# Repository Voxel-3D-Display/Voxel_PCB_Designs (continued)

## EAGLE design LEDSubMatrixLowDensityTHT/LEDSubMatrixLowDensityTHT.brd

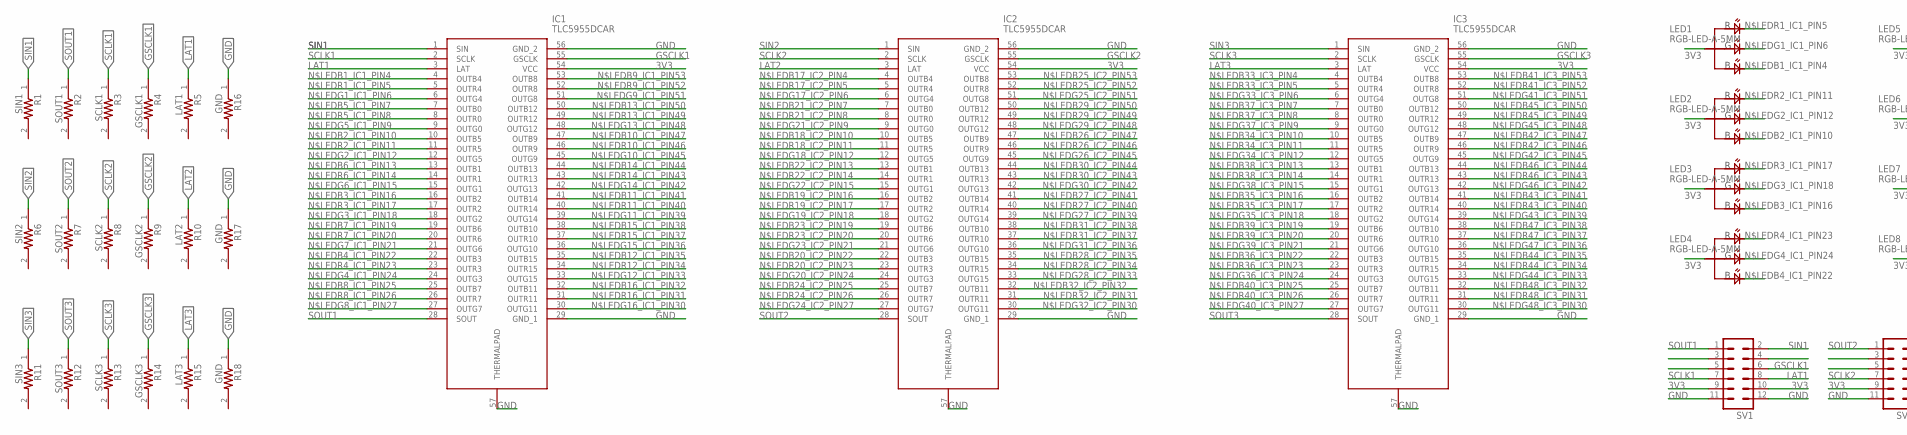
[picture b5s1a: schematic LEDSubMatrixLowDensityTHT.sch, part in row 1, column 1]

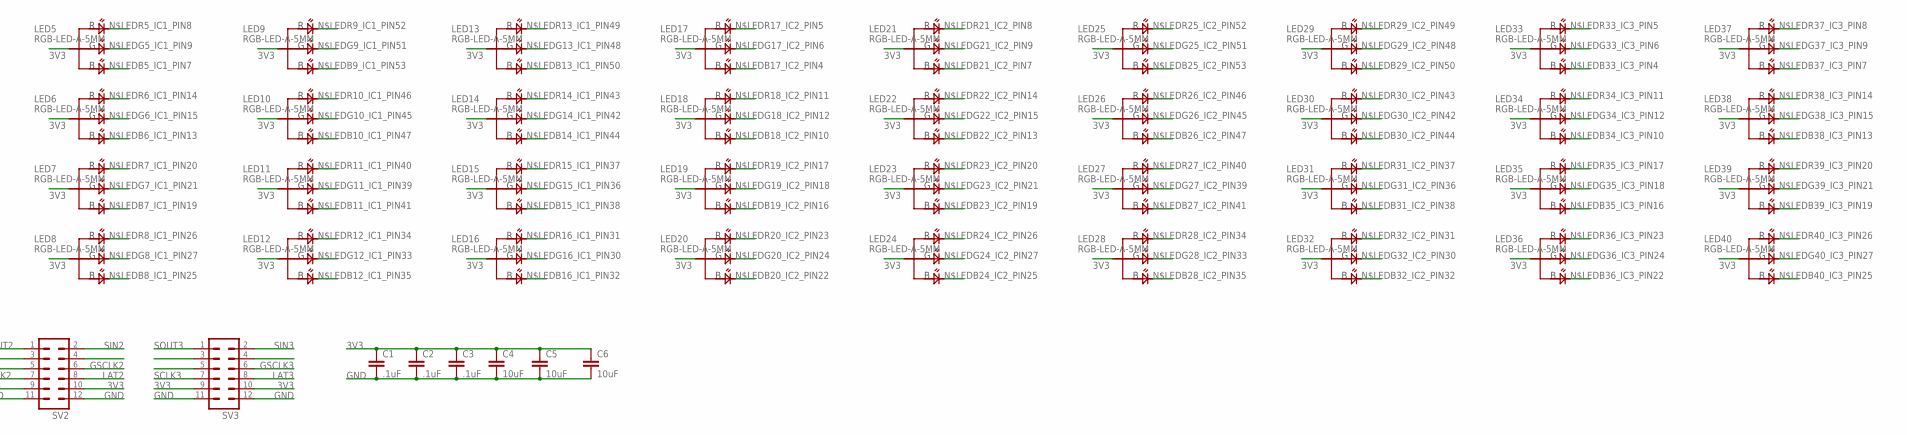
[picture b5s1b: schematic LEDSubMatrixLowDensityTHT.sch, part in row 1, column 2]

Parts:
C1, C2, C3: .1uF; C0603
C4, C5, C6: 10uF; C0805
IC1, IC2, IC3: TLC5955DCAR; SOP50P810X120-57N
LED1, LED2, LED3, LED4, LED5, LED6, LED7, LED8, LED9, LED10, LED11, LED12, LED13, LED14, LED15, LED16, LED17, LED18, LED19, LED20, LED21, LED22, LED23, LED24, LED25, LED26, LED27, LED28, LED29, LED30, LED31, LED32, LED33, LED34, LED35, LED36, LED37, LED38, LED39, LED40: RGB-LED-A-5MM; RGBLED-A-5MM
R1: SIN1; RESC3216X70N
R2: SOUT1; RESC3216X70N
R3: SCLK1; RESC3216X70N
R4: GSCLK1; RESC3216X70N
R5: LAT1; RESC3216X70N
R6: SIN2; RESC3216X70N
R7: SOUT2; RESC3216X70N
R8: SCLK2; RESC3216X70N
R9: GSCLK2; RESC3216X70N
R10: LAT2; RESC3216X70N
R11: SIN3; RESC3216X70N
R12: SOUT3; RESC3216X70N
R13: SCLK3; RESC3216X70N
R14: GSCLK3; RESC3216X70N
R15: LAT3; RESC3216X70N
R16, R17, R18: GND; RESC3216X70N
SV1, SV2, SV3: MA06-2

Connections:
3V3: C1.1, C2.1, C3.1, C4.1, C5.1, C6.1, IC1.54 (VCC), IC2.54 (VCC), IC3.54 (VCC), LED1.AN (COM), LED2.AN (COM), LED3.AN (COM), LED4.AN (COM), LED5.AN (COM), LED6.AN (COM), LED7.AN (COM), LED8.AN (COM), LED9.AN (COM), LED10.AN (COM), LED11.AN (COM), LED12.AN (COM), LED13.AN (COM), LED14.AN (COM), LED15.AN (COM), LED16.AN (COM), LED17.AN (COM), LED18.AN (COM), LED19.AN (COM), LED20.AN (COM), LED21.AN (COM), LED22.AN (COM), LED23.AN (COM), LED24.AN (COM), LED25.AN (COM), LED26.AN (COM), LED27.AN (COM), LED28.AN (COM), LED29.AN (COM), LED30.AN (COM), LED31.AN (COM), LED32.AN (COM), LED33.AN (COM), LED34.AN (COM), LED35.AN (COM), LED36.AN (COM), LED37.AN (COM), LED38.AN (COM), LED39.AN (COM), LED40.AN (COM), SV1.9, SV1.10, SV2.9, SV2.10, SV3.9, SV3.10
GND: C1.2, C2.2, C3.2, C4.2, C5.2, C6.2, IC1.29 (GND_1), IC1.56 (GND_2), IC1.57 (THERMALPAD), IC2.29 (GND_1), IC2.56 (GND_2), IC2.57 (THERMALPAD), IC3.29 (GND_1), IC3.56 (GND_2), IC3.57 (THERMALPAD), R16.1, R17.1, R18.1, SV1.11, SV1.12, SV2.11, SV2.12, SV3.11, SV3.12
GSCLK1: IC1.55 (GSCLK), R4.1, SV1.6
GSCLK2: IC2.55 (GSCLK), R9.1, SV2.6
GSCLK3: IC3.55 (GSCLK), R14.1, SV3.6
LAT1: IC1.3 (LAT), R5.1, SV1.8
LAT2: IC2.3 (LAT), R10.1, SV2.8
LAT3: IC3.3 (LAT), R15.1, SV3.8
N$LEDB1_IC1_PIN4: IC1.4 (OUTB4), LED1.B (BLUE)
N$LEDB2_IC1_PIN10: IC1.10 (OUTB5), LED2.B (BLUE)
N$LEDB3_IC1_PIN16: IC1.16 (OUTB2), LED3.B (BLUE)
N$LEDB4_IC1_PIN22: IC1.22 (OUTB3), LED4.B (BLUE)
N$LEDB5_IC1_PIN7: IC1.7 (OUTB0), LED5.B (BLUE)
N$LEDB6_IC1_PIN13: IC1.13 (OUTB1), LED6.B (BLUE)
N$LEDB7_IC1_PIN19: IC1.19 (OUTB6), LED7.B (BLUE)
N$LEDB8_IC1_PIN25: IC1.25 (OUTB7), LED8.B (BLUE)
N$LEDB9_IC1_PIN53: IC1.53 (OUTB8), LED9.B (BLUE)
N$LEDB10_IC1_PIN47: IC1.47 (OUTB9), LED10.B (BLUE)
N$LEDB11_IC1_PIN41: IC1.41 (OUTB14), LED11.B (BLUE)
N$LEDB12_IC1_PIN35: IC1.35 (OUTB15), LED12.B (BLUE)
N$LEDB13_IC1_PIN50: IC1.50 (OUTB12), LED13.B (BLUE)
N$LEDB14_IC1_PIN44: IC1.44 (OUTB13), LED14.B (BLUE)
N$LEDB15_IC1_PIN38: IC1.38 (OUTB10), LED15.B (BLUE)
N$LEDB16_IC1_PIN32: IC1.32 (OUTB11), LED16.B (BLUE)
N$LEDB17_IC2_PIN4: IC2.4 (OUTB4), LED17.B (BLUE)
N$LEDB18_IC2_PIN10: IC2.10 (OUTB5), LED18.B (BLUE)
N$LEDB19_IC2_PIN16: IC2.16 (OUTB2), LED19.B (BLUE)
N$LEDB20_IC2_PIN22: IC2.22 (OUTB3), LED20.B (BLUE)
N$LEDB21_IC2_PIN7: IC2.7 (OUTB0), LED21.B (BLUE)
N$LEDB22_IC2_PIN13: IC2.13 (OUTB1), LED22.B (BLUE)
N$LEDB23_IC2_PIN19: IC2.19 (OUTB6), LED23.B (BLUE)
N$LEDB24_IC2_PIN25: IC2.25 (OUTB7), LED24.B (BLUE)
N$LEDB25_IC2_PIN53: IC2.53 (OUTB8), LED25.B (BLUE)
N$LEDB26_IC2_PIN47: IC2.47 (OUTB9), LED26.B (BLUE)
N$LEDB27_IC2_PIN41: IC2.41 (OUTB14), LED27.B (BLUE)
N$LEDB28_IC2_PIN35: IC2.35 (OUTB15), LED28.B (BLUE)
N$LEDB29_IC2_PIN50: IC2.50 (OUTB12), LED29.B (BLUE)
N$LEDB30_IC2_PIN44: IC2.44 (OUTB13), LED30.B (BLUE)
N$LEDB31_IC2_PIN38: IC2.38 (OUTB10), LED31.B (BLUE)
N$LEDB32_IC2_PIN32: IC2.32 (OUTB11), LED32.B (BLUE)
N$LEDB33_IC3_PIN4: IC3.4 (OUTB4), LED33.B (BLUE)
N$LEDB34_IC3_PIN10: IC3.10 (OUTB5), LED34.B (BLUE)
N$LEDB35_IC3_PIN16: IC3.16 (OUTB2), LED35.B (BLUE)
N$LEDB36_IC3_PIN22: IC3.22 (OUTB3), LED36.B (BLUE)
N$LEDB37_IC3_PIN7: IC3.7 (OUTB0), LED37.B (BLUE)
N$LEDB38_IC3_PIN13: IC3.13 (OUTB1), LED38.B (BLUE)
N$LEDB39_IC3_PIN19: IC3.19 (OUTB6), LED39.B (BLUE)
N$LEDB40_IC3_PIN25: IC3.25 (OUTB7), LED40.B (BLUE)
N$LEDB41_IC3_PIN53: IC3.53 (OUTB8)
N$LEDB42_IC3_PIN47: IC3.47 (OUTB9)
N$LEDB43_IC3_PIN41: IC3.41 (OUTB14)
N$LEDB44_IC3_PIN35: IC3.35 (OUTB15)
N$LEDB45_IC3_PIN50: IC3.50 (OUTB12)
N$LEDB46_IC3_PIN44: IC3.44 (OUTB13)
N$LEDB47_IC3_PIN38: IC3.38 (OUTB10)
N$LEDB48_IC3_PIN32: IC3.32 (OUTB11)
N$LEDG1_IC1_PIN6: IC1.6 (OUTG4), LED1.G (GREEN)
N$LEDG2_IC1_PIN12: IC1.12 (OUTG5), LED2.G (GREEN)
N$LEDG3_IC1_PIN18: IC1.18 (OUTG2), LED3.G (GREEN)
N$LEDG4_IC1_PIN24: IC1.24 (OUTG3), LED4.G (GREEN)
N$LEDG5_IC1_PIN9: IC1.9 (OUTG0), LED5.G (GREEN)
N$LEDG6_IC1_PIN15: IC1.15 (OUTG1), LED6.G (GREEN)
N$LEDG7_IC1_PIN21: IC1.21 (OUTG6), LED7.G (GREEN)
N$LEDG8_IC1_PIN27: IC1.27 (OUTG7), LED8.G (GREEN)
N$LEDG9_IC1_PIN51: IC1.51 (OUTG8), LED9.G (GREEN)
N$LEDG10_IC1_PIN45: IC1.45 (OUTG9), LED10.G (GREEN)
N$LEDG11_IC1_PIN39: IC1.39 (OUTG14), LED11.G (GREEN)
N$LEDG12_IC1_PIN33: IC1.33 (OUTG15), LED12.G (GREEN)
N$LEDG13_IC1_PIN48: IC1.48 (OUTG12), LED13.G (GREEN)
N$LEDG14_IC1_PIN42: IC1.42 (OUTG13), LED14.G (GREEN)
N$LEDG15_IC1_PIN36: IC1.36 (OUTG10), LED15.G (GREEN)
N$LEDG16_IC1_PIN30: IC1.30 (OUTG11), LED16.G (GREEN)
N$LEDG17_IC2_PIN6: IC2.6 (OUTG4), LED17.G (GREEN)
N$LEDG18_IC2_PIN12: IC2.12 (OUTG5), LED18.G (GREEN)
N$LEDG19_IC2_PIN18: IC2.18 (OUTG2), LED19.G (GREEN)
N$LEDG20_IC2_PIN24: IC2.24 (OUTG3), LED20.G (GREEN)
N$LEDG21_IC2_PIN9: IC2.9 (OUTG0), LED21.G (GREEN)
N$LEDG22_IC2_PIN15: IC2.15 (OUTG1), LED22.G (GREEN)
N$LEDG23_IC2_PIN21: IC2.21 (OUTG6), LED23.G (GREEN)
N$LEDG24_IC2_PIN27: IC2.27 (OUTG7), LED24.G (GREEN)
N$LEDG25_IC2_PIN51: IC2.51 (OUTG8), LED25.G (GREEN)
N$LEDG26_IC2_PIN45: IC2.45 (OUTG9), LED26.G (GREEN)
N$LEDG27_IC2_PIN39: IC2.39 (OUTG14), LED27.G (GREEN)
N$LEDG28_IC2_PIN33: IC2.33 (OUTG15), LED28.G (GREEN)
N$LEDG29_IC2_PIN48: IC2.48 (OUTG12), LED29.G (GREEN)
N$LEDG30_IC2_PIN42: IC2.42 (OUTG13), LED30.G (GREEN)
N$LEDG31_IC2_PIN36: IC2.36 (OUTG10), LED31.G (GREEN)
N$LEDG32_IC2_PIN30: IC2.30 (OUTG11), LED32.G (GREEN)
N$LEDG33_IC3_PIN6: IC3.6 (OUTG4), LED33.G (GREEN)
N$LEDG34_IC3_PIN12: IC3.12 (OUTG5), LED34.G (GREEN)
N$LEDG35_IC3_PIN18: IC3.18 (OUTG2), LED35.G (GREEN)
N$LEDG36_IC3_PIN24: IC3.24 (OUTG3), LED36.G (GREEN)
N$LEDG37_IC3_PIN9: IC3.9 (OUTG0), LED37.G (GREEN)
N$LEDG38_IC3_PIN15: IC3.15 (OUTG1), LED38.G (GREEN)
N$LEDG39_IC3_PIN21: IC3.21 (OUTG6), LED39.G (GREEN)
N$LEDG40_IC3_PIN27: IC3.27 (OUTG7), LED40.G (GREEN)
N$LEDG41_IC3_PIN51: IC3.51 (OUTG8)
N$LEDG42_IC3_PIN45: IC3.45 (OUTG9)
N$LEDG43_IC3_PIN39: IC3.39 (OUTG14)
N$LEDG44_IC3_PIN33: IC3.33 (OUTG15)
N$LEDG45_IC3_PIN48: IC3.48 (OUTG12)
N$LEDG46_IC3_PIN42: IC3.42 (OUTG13)
N$LEDG47_IC3_PIN36: IC3.36 (OUTG10)
N$LEDG48_IC3_PIN30: IC3.30 (OUTG11)
N$LEDR1_IC1_PIN5: IC1.5 (OUTR4), LED1.R (RED)
N$LEDR2_IC1_PIN11: IC1.11 (OUTR5), LED2.R (RED)
N$LEDR3_IC1_PIN17: IC1.17 (OUTR2), LED3.R (RED)
N$LEDR4_IC1_PIN23: IC1.23 (OUTR3), LED4.R (RED)
N$LEDR5_IC1_PIN8: IC1.8 (OUTR0), LED5.R (RED)
N$LEDR6_IC1_PIN14: IC1.14 (OUTR1), LED6.R (RED)
N$LEDR7_IC1_PIN20: IC1.20 (OUTR6), LED7.R (RED)
N$LEDR8_IC1_PIN26: IC1.26 (OUTR7), LED8.R (RED)
N$LEDR9_IC1_PIN52: IC1.52 (OUTR8), LED9.R (RED)
N$LEDR10_IC1_PIN46: IC1.46 (OUTR9), LED10.R (RED)
N$LEDR11_IC1_PIN40: IC1.40 (OUTR14), LED11.R (RED)
N$LEDR12_IC1_PIN34: IC1.34 (OUTR15), LED12.R (RED)
N$LEDR13_IC1_PIN49: IC1.49 (OUTR12), LED13.R (RED)
N$LEDR14_IC1_PIN43: IC1.43 (OUTR13), LED14.R (RED)
N$LEDR15_IC1_PIN37: IC1.37 (OUTR10), LED15.R (RED)
N$LEDR16_IC1_PIN31: IC1.31 (OUTR11), LED16.R (RED)
N$LEDR17_IC2_PIN5: IC2.5 (OUTR4), LED17.R (RED)
N$LEDR18_IC2_PIN11: IC2.11 (OUTR5), LED18.R (RED)
N$LEDR19_IC2_PIN17: IC2.17 (OUTR2), LED19.R (RED)
N$LEDR20_IC2_PIN23: IC2.23 (OUTR3), LED20.R (RED)
N$LEDR21_IC2_PIN8: IC2.8 (OUTR0), LED21.R (RED)
N$LEDR22_IC2_PIN14: IC2.14 (OUTR1), LED22.R (RED)
N$LEDR23_IC2_PIN20: IC2.20 (OUTR6), LED23.R (RED)
N$LEDR24_IC2_PIN26: IC2.26 (OUTR7), LED24.R (RED)
N$LEDR25_IC2_PIN52: IC2.52 (OUTR8), LED25.R (RED)
N$LEDR26_IC2_PIN46: IC2.46 (OUTR9), LED26.R (RED)
N$LEDR27_IC2_PIN40: IC2.40 (OUTR14), LED27.R (RED)
N$LEDR28_IC2_PIN34: IC2.34 (OUTR15), LED28.R (RED)
N$LEDR29_IC2_PIN49: IC2.49 (OUTR12), LED29.R (RED)
N$LEDR30_IC2_PIN43: IC2.43 (OUTR13), LED30.R (RED)
N$LEDR31_IC2_PIN37: IC2.37 (OUTR10), LED31.R (RED)
N$LEDR32_IC2_PIN31: IC2.31 (OUTR11), LED32.R (RED)
N$LEDR33_IC3_PIN5: IC3.5 (OUTR4), LED33.R (RED)
N$LEDR34_IC3_PIN11: IC3.11 (OUTR5), LED34.R (RED)
N$LEDR35_IC3_PIN17: IC3.17 (OUTR2), LED35.R (RED)
N$LEDR36_IC3_PIN23: IC3.23 (OUTR3), LED36.R (RED)
N$LEDR37_IC3_PIN8: IC3.8 (OUTR0), LED37.R (RED)
N$LEDR38_IC3_PIN14: IC3.14 (OUTR1), LED38.R (RED)
N$LEDR39_IC3_PIN20: IC3.20 (OUTR6), LED39.R (RED)
N$LEDR40_IC3_PIN26: IC3.26 (OUTR7), LED40.R (RED)
N$LEDR41_IC3_PIN52: IC3.52 (OUTR8)
N$LEDR42_IC3_PIN46: IC3.46 (OUTR9)
N$LEDR43_IC3_PIN40: IC3.40 (OUTR14)
N$LEDR44_IC3_PIN34: IC3.34 (OUTR15)
N$LEDR45_IC3_PIN49: IC3.49 (OUTR12)
N$LEDR46_IC3_PIN43: IC3.43 (OUTR13)
N$LEDR47_IC3_PIN37: IC3.37 (OUTR10)
N$LEDR48_IC3_PIN31: IC3.31 (OUTR11)
SCLK1: IC1.2 (SCLK), R3.1, SV1.7
SCLK2: IC2.2 (SCLK), R8.1, SV2.7
SCLK3: IC3.2 (SCLK), R13.1, SV3.7
SIN1: IC1.1 (SIN), R1.1, SV1.2
SIN2: IC2.1 (SIN), R6.1, SV2.2
SIN3: IC3.1 (SIN), R11.1, SV3.2
SOUT1: IC1.28 (SOUT), R2.1, SV1.1
SOUT2: IC2.28 (SOUT), R7.1, SV2.1
SOUT3: IC3.28 (SOUT), R12.1, SV3.1

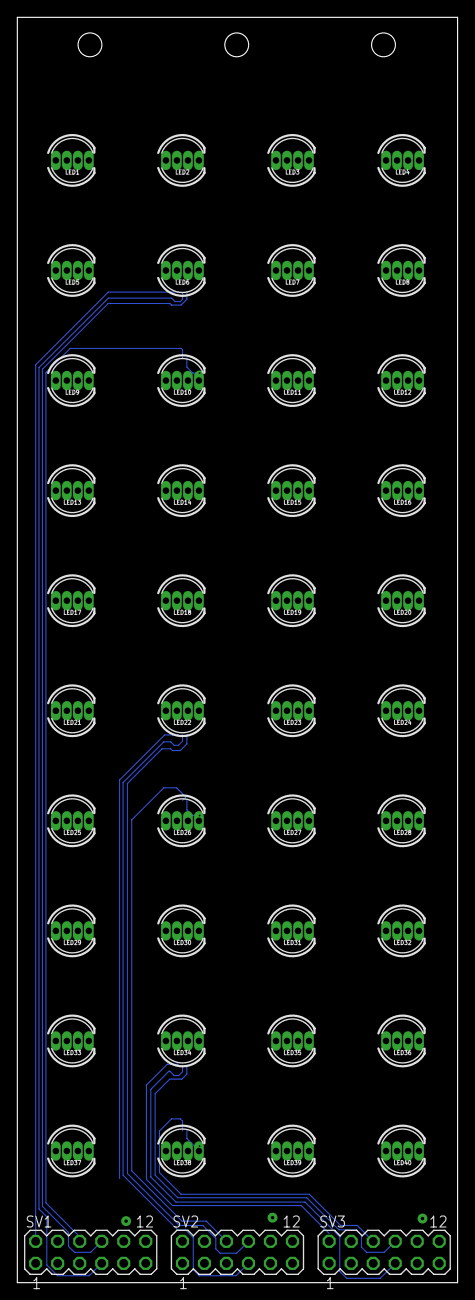
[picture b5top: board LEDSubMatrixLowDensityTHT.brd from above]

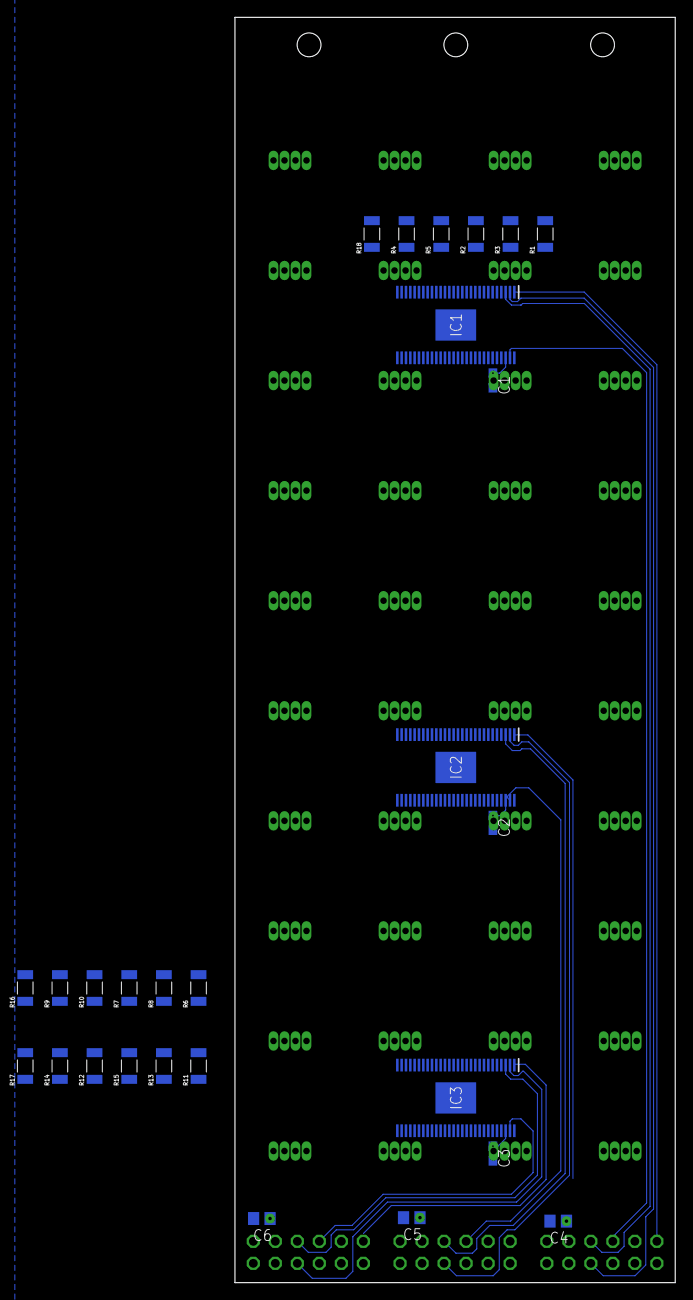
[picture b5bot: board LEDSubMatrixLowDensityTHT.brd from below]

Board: 2 copper layers, 50.8 x 146.0 mm, 70 parts (27 on the bottom side), 137 nets.

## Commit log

2021-10-13 Initial High Density PCB
2021-10-21 Automated Python scripts and one block of LED matrix
    Added a bunch of python scripts for automating Eagle design. Created a template for one LED driver block of board (to be copied later)
2021-10-28 added pictures of led matrix pcbs
2021-11-06 Finished placing all LEDs and Led Drivers
2021-11-06 Routed all the signals from the FPGA
2021-11-10 Finished routing traces on high density matrix PCB
2021-11-10 High density PCB fixes
    Fixed airwires errors and grouped components on schematic
2022-01-14 Finalized LED Matrix schematic and board files
2022-01-14 gerber files generated; cleanup
2022-01-15 fixed problem of not having pairs of drivers daisy-chained
2022-01-22 created rev2 for high density led matrix PCB
2022-01-22 lib additions for controls pcb
2022-01-22 Added RasPi EAGLE Lib
2022-01-23 Added Pololu buck regulators
2022-01-23 more lib additions
2022-01-23 Added DE0-Nano
2022-01-23 Added logic buffer
2022-01-23 power schematic and library additions
2022-01-24 finished rev 2 of PCB submatrix led
2022-01-30 controls layout partial
2022-01-30 parts exchange, layout corrections, no routing
2022-01-30 Fixed encoder on spinning controls board
2022-01-31 Added Motor Controller PCB
2022-01-31 Added button input
2022-01-31 schem FPGA pins, partial
2022-01-31 full schematic, silkscreen cleanup
2022-01-31 Started some traces
2022-01-31 Updated Eagle Lib
2022-01-31 Finished power routing and other minor changes
2022-01-31 Finished controls board, added gerbers
2022-01-31 Cleaned schematics, added pdfs
2022-01-31 Added some silk screen
2022-01-31 Updated pinouts to align with control board
2022-01-31 reuploaded gerber files
2022-01-31 added pdf schematic of led matrix pcb
2022-02-01 Added logic buffers to LED matrix
2022-02-01 Fixes to controls board
2022-02-01 routed logic buffers on matrix pcb
2022-02-01 Added logic level shifter
2022-02-01 dan changes + lib
2022-02-01 fixed soldermask on led submatrix
2022-02-01 dan tings, 50ohm FPGA inline, 3v3 to 5 logic for SR
2022-02-01 to-kyle documentation updates
2022-02-01 full routing layout and schematic
2022-02-01 added mounting holes; processed CAM and schem PDF
2022-03-18 silkscreen update
2022-03-18 fixed gerbers
2022-03-18 bleck
2022-03-18 added v3 of submatrix PCB
2022-03-19 Added newly ordered controls board gerbers
2022-03-30 renamed 2x13 header silk screen
2022-04-16 Added KiCAD Files
